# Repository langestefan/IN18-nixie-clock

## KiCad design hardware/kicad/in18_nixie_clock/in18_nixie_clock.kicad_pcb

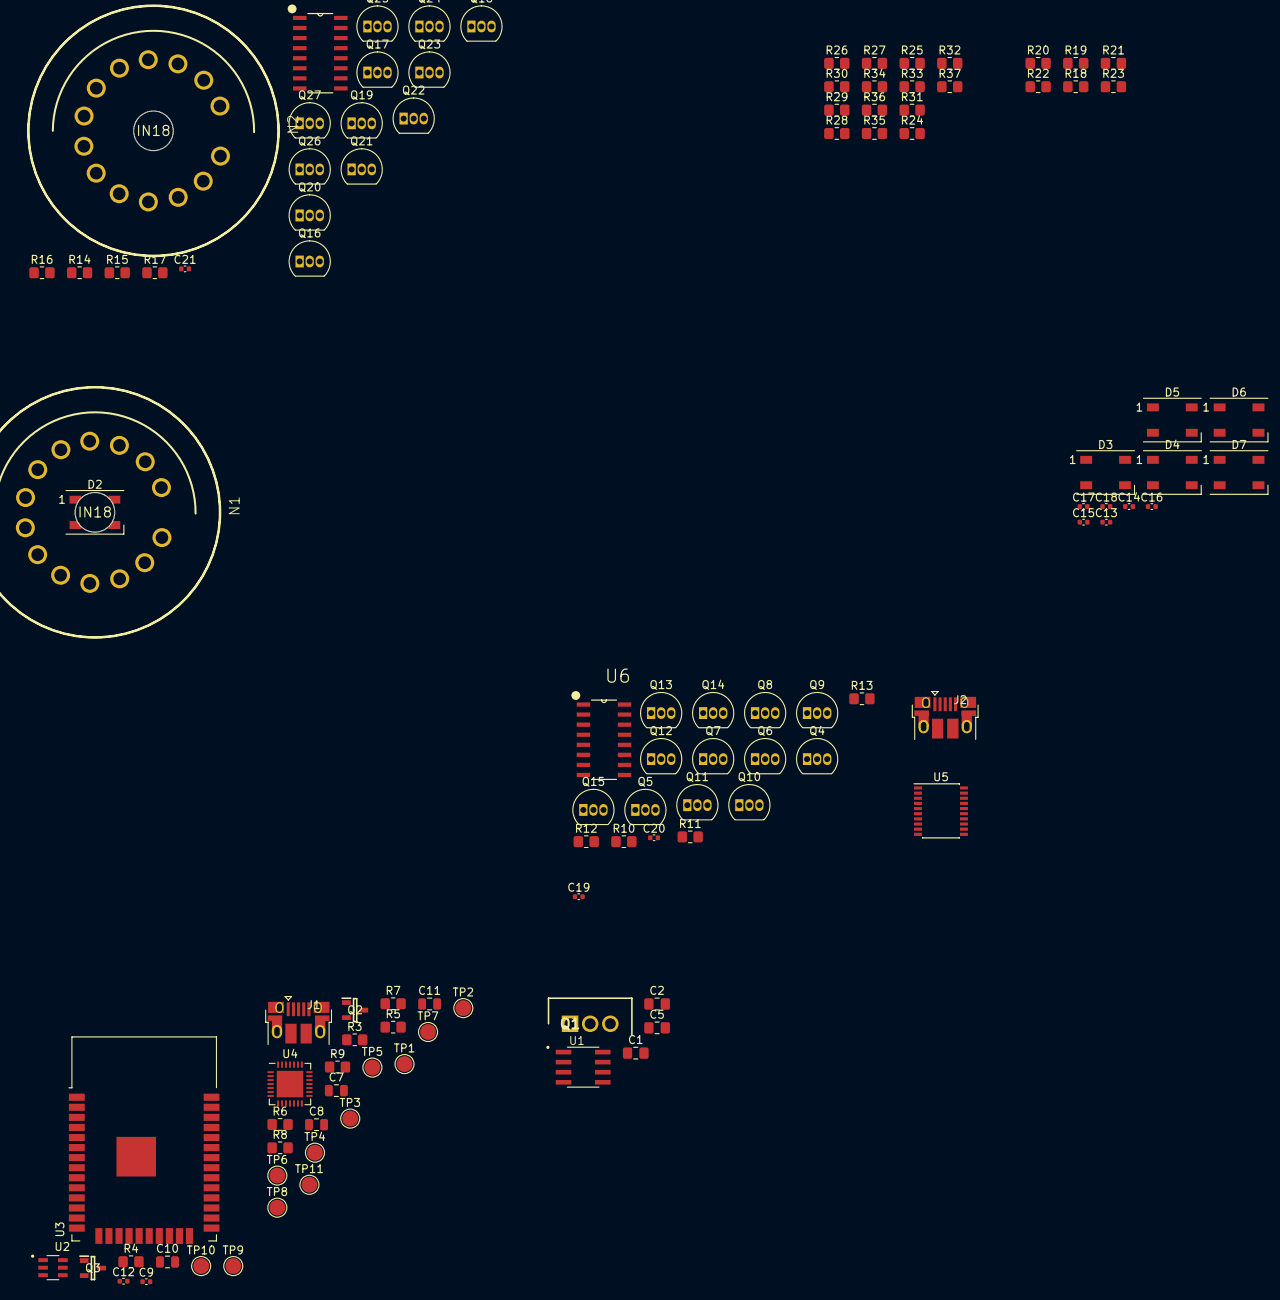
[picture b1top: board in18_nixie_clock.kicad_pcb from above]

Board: 2 copper layers, 108 parts (0 on the bottom side), 105 nets, no tracks yet.

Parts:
C1, C2: 100nF; C_0805_2012Metric_Pad1.18x1.45mm_HandSolder
C5: 100nF, 250V; C_0805_2012Metric_Pad1.18x1.45mm_HandSolder
C7, C8, C10, C11: 10u 35v; C_0805_2012Metric
C9, C12, C13, C14, C15, C16, C17, C18, C19, C20, C21: 100n; C_0402_1005Metric
D2, D3, D4, D5, D6, D7: WS2812B; LED_WS2812B_PLCC4_5.0x5.0mm_P3.2mm
J1, J2: USB_B_Micro; USB_Micro-B_EDAC_UCON00686
N1, N2: IN18; nixies-us-IN-18-DSUB
Q1: IRF644PBF; TO254P465X1024X2050-3P
Q2, Q3: SS8050-G; SOT95P240X115-3N
Q4, Q5, Q6, Q7, Q8, Q9, Q11, Q12, Q13, Q14, Q15, Q16, Q17, Q18, Q19, Q20, Q21, Q23, Q24, Q25, Q26, Q27: MPSA42; TO-92_Inline
Q10, Q22: MPSA92; TO-92_Inline
R3: 2K; R_0805_2012Metric_Pad1.20x1.40mm_HandSolder
R4, R5: 12K; R_0805_2012Metric_Pad1.20x1.40mm_HandSolder
R6, R7, R8, R9: 0; R_0805_2012Metric_Pad1.20x1.40mm_HandSolder
R10, R11, R12, R14, R17, R19, R20, R21, R22, R23, R24, R25, R26, R28, R31, R33, R34, R35, R36, R37: 10K; R_0805_2012Metric_Pad1.20x1.40mm_HandSolder
R13, R18, R27, R32: 33k; R_0805_2012Metric_Pad1.20x1.40mm_HandSolder
R15, R29: 100K; R_0805_2012Metric_Pad1.20x1.40mm_HandSolder
R16, R30: 470K; R_0805_2012Metric_Pad1.20x1.40mm_HandSolder
TP1: VBUS; TestPoint_Pad_D2.0mm
TP2: TX; TestPoint_Pad_D2.0mm
TP3: RX; TestPoint_Pad_D2.0mm
TP4: CTS; TestPoint_Pad_D2.0mm
TP5: DSR; TestPoint_Pad_D2.0mm
TP6: DCD; TestPoint_Pad_D2.0mm
TP7: RI; TestPoint_Pad_D2.0mm
TP8: PROG_EN; TestPoint_Pad_D2.0mm
TP9: ESP_EN; TestPoint_Pad_D2.0mm
TP10: DTR; TestPoint_Pad_D2.0mm
TP11: RTS; TestPoint_Pad_D2.0mm
U1: MAX1771CSA+; SOIC127P600X175-8N
U2: IP4220CZ6F; SOT95P275X110-6N
U3: ESP32-WROOM-32
U4: CP2102N-Axx-xQFN28; QFN-28-1EP_5x5mm_P0.5mm_EP3.35x3.35mm
U5: PCF8574TS; SSOP-20_4.4x6.5mm_P0.65mm
U6, U7: 74HC42D,652; SOIC127P600X175-16N

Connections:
+3V3: C7.1, C8.1, C9.1, C10.1, C11.1, C12.1, R3.1, U3.2 (VDD), U4.6 (VDD), U4.7 (VREGIN)
+5V: C14.1, C15.1, C16.1, C17.1, C18.1, C19.1, D2.1 (VDD), D3.1 (VDD), D4.1 (VDD), D5.1 (VDD), D6.1 (VDD), D7.1 (VDD)
/hv_supply/+12V: C1.1, C2.1, U1.2 (V+)
/hv_supply/+180V: C5.1, Q10.1 (E), Q22.1 (E), R15.1, R29.1
/in18_nixies/+3V3: C13.1, C20.1, C21.1, U5.5 (VDD), U6.16 (VCC), U7.16 (VCC)
/in18_nixies/A0_H_LS: U5.10 (P0), U5.16 (P4)
/in18_nixies/A1_H_LS: U5.11 (P1), U5.17 (P5)
/in18_nixies/A2_H_LS: U5.12 (P2), U5.19 (P6)
/in18_nixies/A3_H_LS: U5.14 (P3), U5.20 (P7)
/in18_nixies/Nixie hour, least significant/NIXIE_DIGIT_0: Q16.2 (B), R24.2
/in18_nixies/Nixie hour, least significant/NIXIE_DIGIT_1: Q17.2 (B), R25.2
/in18_nixies/Nixie hour, least significant/NIXIE_DIGIT_2: Q18.2 (B), R26.2
/in18_nixies/Nixie hour, least significant/NIXIE_DIGIT_3: Q20.2 (B), R28.2
/in18_nixies/Nixie hour, least significant/NIXIE_DIGIT_4: Q21.2 (B), R31.2
/in18_nixies/Nixie hour, least significant/NIXIE_DIGIT_5: Q23.2 (B), R33.2
/in18_nixies/Nixie hour, least significant/NIXIE_DIGIT_6: Q24.2 (B), R34.2
/in18_nixies/Nixie hour, least significant/NIXIE_DIGIT_7: Q25.2 (B), R35.2
/in18_nixies/Nixie hour, least significant/NIXIE_DIGIT_8: Q26.2 (B), R36.2
/in18_nixies/Nixie hour, least significant/NIXIE_DIGIT_9: Q27.2 (B), R37.2
/in18_nixies/Nixie hour, most significant/NIXIE_DIGIT_0: Q4.2 (B), R10.2
/in18_nixies/Nixie hour, most significant/NIXIE_DIGIT_1: Q5.2 (B), R11.2
/in18_nixies/Nixie hour, most significant/NIXIE_DIGIT_2: Q6.2 (B), R12.2
/in18_nixies/Nixie hour, most significant/NIXIE_DIGIT_3: Q8.2 (B), R14.2
/in18_nixies/Nixie hour, most significant/NIXIE_DIGIT_4: Q9.2 (B), R17.2
/in18_nixies/Nixie hour, most significant/NIXIE_DIGIT_5: Q11.2 (B), R19.2
/in18_nixies/Nixie hour, most significant/NIXIE_DIGIT_6: Q12.2 (B), R20.2
/in18_nixies/Nixie hour, most significant/NIXIE_DIGIT_7: Q13.2 (B), R21.2
/in18_nixies/Nixie hour, most significant/NIXIE_DIGIT_8: Q14.2 (B), R22.2
/in18_nixies/Nixie hour, most significant/NIXIE_DIGIT_9: Q15.2 (B), R23.2
CTS: TP4.1, U4.23 (~CTS)
D+: J1.3 (D+), J2.3 (D+), U2.3 (I/O_2), U4.4 (D+)
D-: J1.2 (D-), J2.2 (D-), U2.1 (I/O_1), U4.5 (D-)
DTR: Q2.2, R5.2, TP10.1, U4.28 (~DTR)
ESP_EN: Q3.3, TP9.1, U3.3 (EN)
ESP_RX: R6.2, R7.2, U3.34 (RXD0/IO3)
ESP_TX: R8.2, R9.2, U3.35 (TXD0/IO1)
GND: C1.2, C2.2, C5.2, C7.2, C8.2, C9.2, C10.2, C11.2, C12.2, C13.2, C14.2, C15.2, C16.2, C17.2, C18.2, C19.2, C20.2, C21.2, D2.3 (VSS), D3.3 (VSS), D4.3 (VSS), D5.3 (VSS), D6.3 (VSS), D7.3 (VSS), J1.5 (GND), J1.6 (Shield), J2.5 (GND), J2.6 (Shield), Q4.1 (E), Q5.1 (E), Q6.1 (E), Q7.1 (E), Q8.1 (E), Q9.1 (E), Q11.1 (E), Q12.1 (E), Q13.1 (E), Q14.1 (E), Q15.1 (E), Q16.1 (E), Q17.1 (E), Q18.1 (E), Q19.1 (E), Q20.1 (E), Q21.1 (E), Q23.1 (E), Q24.1 (E), Q25.1 (E), Q26.1 (E), Q27.1 (E), U1.5 (REF), U1.6 (AGND), U1.7 (GND), U2.2 (GND), U3.1 (GND), U3.15 (GND), U3.38 (GND), U3.39 (GND), U4.3 (GND), U4.29 (GND), U5.15 (VSS), U6.8 (GND), U7.8 (GND)
unnamed: D2.2 (DOUT), D3.4 (DIN)
unnamed: D3.2 (DOUT), D4.4 (DIN)
unnamed: D4.2 (DOUT), D5.4 (DIN)
unnamed: D5.2 (DOUT), D6.4 (DIN)
unnamed: D6.2 (DOUT), D7.4 (DIN)
unnamed: N1.0, Q4.3 (C)
unnamed: N1.1, Q5.3 (C)
unnamed: N1.2, Q6.3 (C)
unnamed: N1.3, Q8.3 (C)
unnamed: N1.4, Q9.3 (C)
unnamed: N1.5, Q11.3 (C)
unnamed: N1.6, Q12.3 (C)
unnamed: N1.7, Q13.3 (C)
unnamed: N1.8, Q14.3 (C)
unnamed: N1.9, Q15.3 (C)
unnamed: N1.A, R18.2
unnamed: N2.0, Q16.3 (C)
unnamed: N2.1, Q17.3 (C)
unnamed: N2.2, Q18.3 (C)
unnamed: N2.3, Q20.3 (C)
unnamed: N2.4, Q21.3 (C)
unnamed: N2.5, Q23.3 (C)
unnamed: N2.6, Q24.3 (C)
unnamed: N2.7, Q25.3 (C)
unnamed: N2.8, Q26.3 (C)
unnamed: N2.9, Q27.3 (C)
unnamed: N2.A, R32.2
unnamed: Q1.1 (G), U1.1 (EXT)
unnamed: Q1.3 (S), U1.8 (CS)
unnamed: Q2.1, R4.1
unnamed: Q3.1, R5.1
unnamed: Q7.2 (B), R13.1
unnamed: Q7.3 (C), R16.2
unnamed: Q10.2 (B), R15.2, R16.1
unnamed: Q10.3 (C), R18.1
unnamed: Q19.2 (B), R27.1
unnamed: Q19.3 (C), R30.2
unnamed: Q22.2 (B), R29.2, R30.1
unnamed: Q22.3 (C), R32.1
unnamed: R3.2, U4.9 (~RST)
unnamed: R10.1, U6.1 (~Y0)
unnamed: R11.1, U6.2 (~Y1)
unnamed: R12.1, U6.3 (~Y2)
unnamed: R14.1, U6.4 (~Y3)
unnamed: R17.1, U6.5 (~Y4)
unnamed: R19.1, U6.6 (~Y5)
unnamed: R20.1, U6.7 (~Y6)
unnamed: R21.1, U6.9 (~Y7)
unnamed: R22.1, U6.10 (~Y8)
unnamed: R23.1, U6.11 (~Y9)
unnamed: R24.1, U7.1 (~Y0)
unnamed: R25.1, U7.2 (~Y1)
unnamed: R26.1, U7.3 (~Y2)
unnamed: R28.1, U7.4 (~Y3)
unnamed: R31.1, U7.5 (~Y4)
unnamed: R33.1, U7.6 (~Y5)
unnamed: R34.1, U7.7 (~Y6)
unnamed: R35.1, U7.9 (~Y7)
unnamed: R36.1, U7.10 (~Y8)
unnamed: R37.1, U7.11 (~Y9)
unnamed: TP5.1, U4.27 (~DSR)
unnamed: TP6.1, U4.1 (~DCD)
unnamed: TP7.1, U4.2 (~RI/CLK)
PROG_EN: Q2.3, TP8.1, U3.25 (IO0)
RTS: Q3.2, R4.2, TP11.1, U4.24 (~RTS)
RXD: R7.1, R9.1, TP3.1, U4.25 (RXD)
TXD: R6.1, R8.1, TP2.1, U4.26 (TXD)
VBUS: J1.1 (VBUS), J2.1 (VBUS), TP1.1, U2.5 (VP), U4.8 (VBUS)

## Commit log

2021-06-20 Add some schematic files
2021-06-20 Modify gitignore
2021-06-26 Add several schematics
